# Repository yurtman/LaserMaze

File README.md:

LaserMaze is an exciting game that imitates the comically bad kind of laser security system found in heist movies. Using Arduino, augmented laser pointers, and a smoke machine, LaserMaze can transform any shipping container or hallway into a practice course for aspiring special agents.

It is currently still very much a prototype and the documentation of the project reflects this. For the most up to date documentation please see the [wiki](https://github.com/yurtman/LaserMaze/wiki).

##Features
- Made with easy to source components (laserpointers, basic electronics)
- Entrance/exit portal to start and stop the timer
- Auto calibration
- Steal detection (item to be stolen can be easily customised)
- Alarm sequence
- Open source

###Not yet implemented but being worked on:
- GUI to display high scores and alignment status (done in the processing language)
- scaling to the arduino Mega to include more lasers
- LED alarm lights integrated with the hardware and code
- sound effects and speaker (Alarm, Maze Active, enter the maze)
- expanding the current positioning strategies
- wireless communication and battery modules

###Abandoned goals:
- videofeed so attendant doens't need to stand inside the smoke filled container the whole day (IR light is also blocked by smoke... duh!)
- moving lasers (nice in the movies, very hard to actually make)

##Examples of use
The LaserMaze started as a hobby project with humble beginnings- a rats nest of alligator clips. 

Since then development has not improved much but the experience resonates well with audiences of all ages and the prototype has already been used for quite a few events:
####Orbit Festival (21st Dec 2014)

####Open day De Jonge Onderzoekers (14th Feb 2015)

####Maak Festival Groningen (12th Apr 2015)

####Night of Art and Science (5th Jun 2015)

####Noorderzon Festival (26th-30th Aug 2015)

####Kinderboekenweek (10th Oct 2015)

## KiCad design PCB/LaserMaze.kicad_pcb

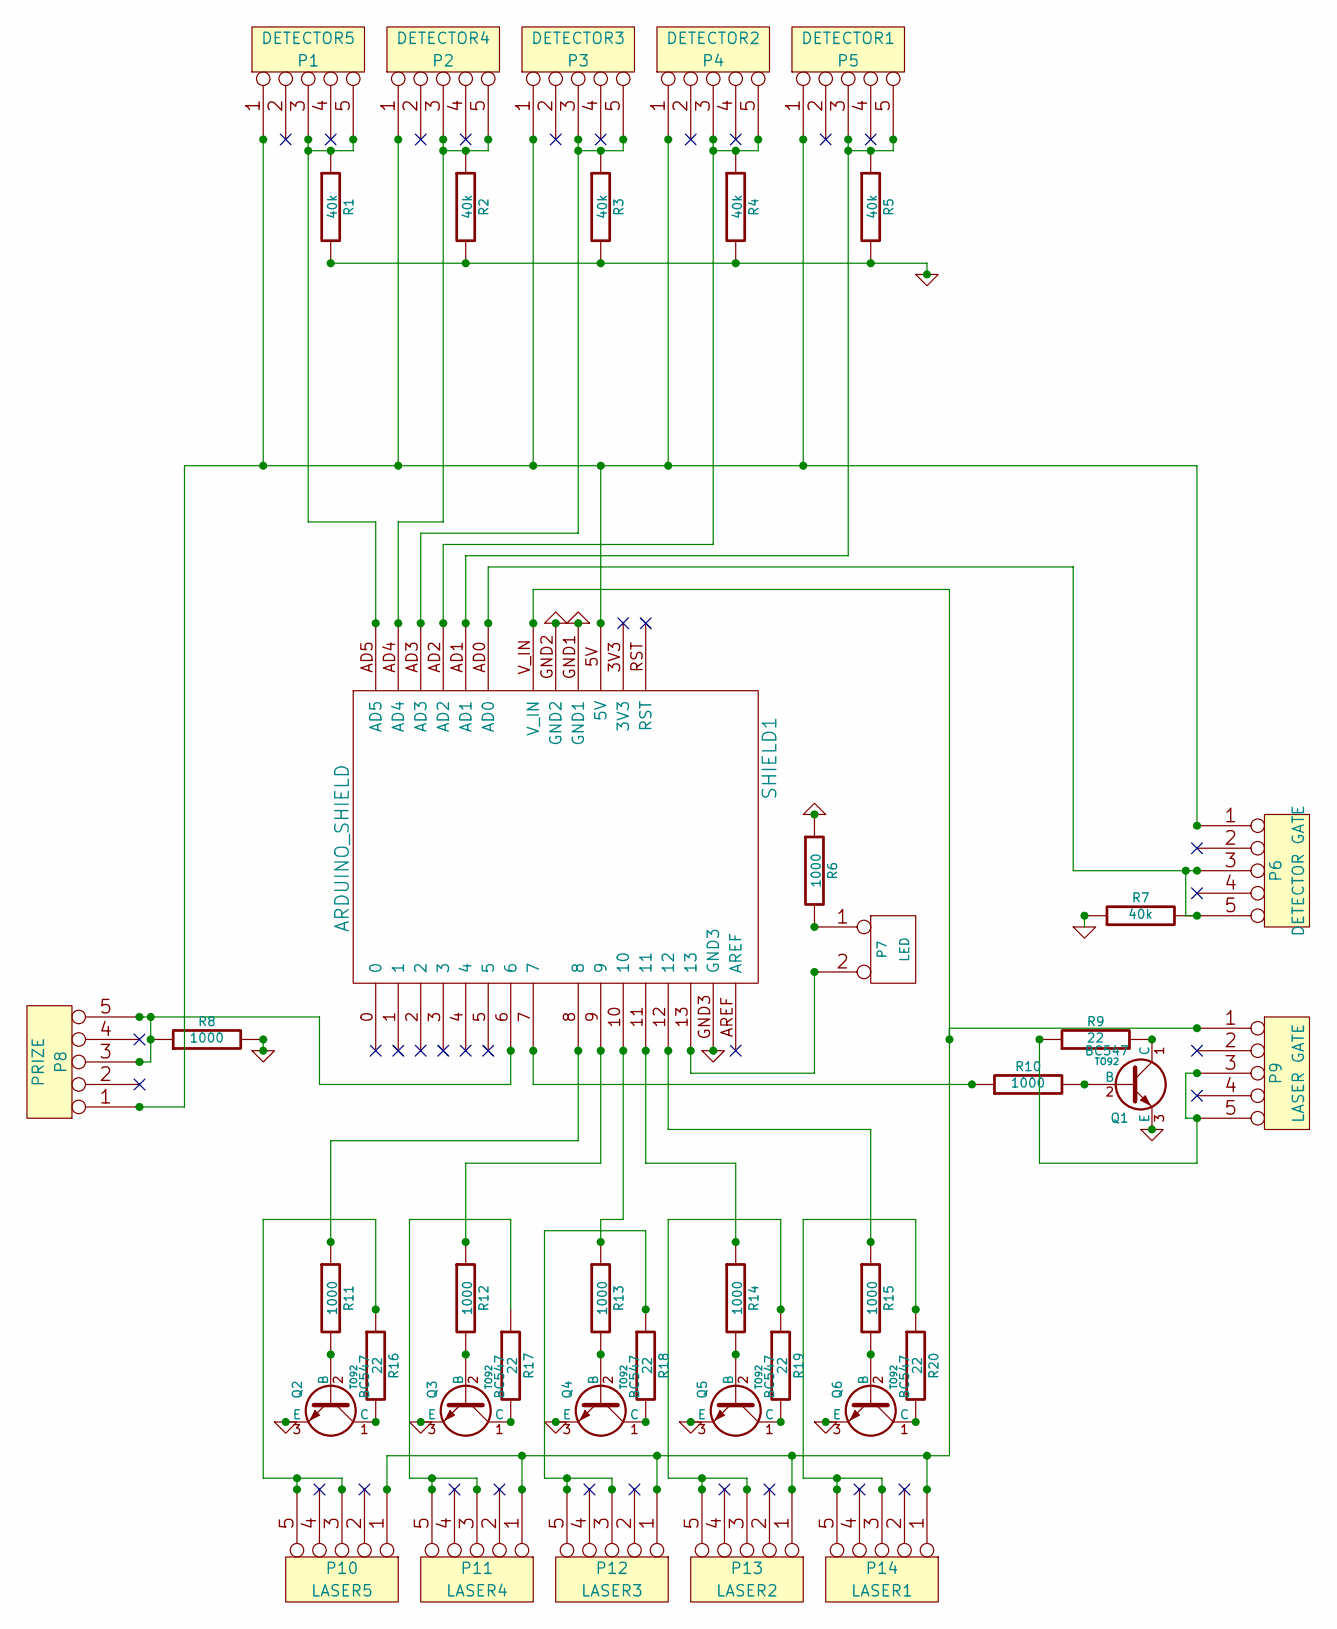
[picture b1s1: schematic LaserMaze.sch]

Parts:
P1: DETECTOR5
P2: DETECTOR4
P3: DETECTOR3
P4: DETECTOR2
P5: DETECTOR1
P6: DETECTOR GATE
P7: LED
P8: PRIZE
P9: LASER GATE
P10: LASER5
P11: LASER4
P12: LASER3
P13: LASER2
P14: LASER1
Q1, Q2, Q3, Q4, Q5, Q6: BC547; TO92
R1, R2, R3, R4, R5, R7: 40k
R6, R8, R10, R11, R12, R13, R14, R15: 1000
R9, R16, R17, R18, R19, R20: 22
SHIELD1: ARDUINO_SHIELD

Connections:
GND: Q1.3 (E), Q2.3 (E), Q3.3 (E), Q4.3 (E), Q5.3 (E), Q6.3 (E), R1.2, R2.2, R3.2, R4.2, R5.2, R6.1, R7.1, R8.2, SHIELD1.GND1, SHIELD1.GND2, SHIELD1.GND3
unnamed: P9.1, P10.1, P11.1, P12.1, P13.1, P14.1, SHIELD1.V_IN
unnamed: P7.2 (PM), SHIELD1.13
unnamed: R15.1, SHIELD1.12
unnamed: R14.1, SHIELD1.11
unnamed: P1.1, P2.1, P3.1, P4.1, P5.1, P6.1, P8.1, SHIELD1.5V
unnamed: P9.3, P9.5, R9.1
unnamed: R13.1, SHIELD1.10
unnamed: R12.1, SHIELD1.9
unnamed: R11.1, SHIELD1.8
unnamed: R10.1, SHIELD1.7
unnamed: P6.3, P6.5, R7.2, SHIELD1.AD0
unnamed: Q3.2 (B), R12.2
unnamed: Q1.2 (B), R10.2
unnamed: Q1.1 (C), R9.2
unnamed: Q6.2 (B), R15.2
unnamed: Q6.1 (C), R20.2
unnamed: Q5.2 (B), R14.2
unnamed: Q5.1 (C), R19.2
unnamed: Q4.2 (B), R13.2
unnamed: Q4.1 (C), R18.2
unnamed: Q3.1 (C), R17.2
unnamed: Q2.2 (B), R11.2
unnamed: Q2.1 (C), R16.2
unnamed: P1.3, P1.5, R1.1, SHIELD1.AD5
unnamed: P2.3, P2.5, R2.1, SHIELD1.AD4
unnamed: P8.3, P8.5, R8.1, SHIELD1.6
unnamed: P13.3, P13.5, R19.1
unnamed: P12.3, P12.5, R18.1
unnamed: P11.3, P11.5, R17.1
unnamed: P14.3, P14.5, R20.1
unnamed: P10.3, P10.5, R16.1
unnamed: P3.3, P3.5, R3.1, SHIELD1.AD3
unnamed: P4.3, P4.5, R4.1, SHIELD1.AD2
unnamed: P5.3, P5.5, R5.1, SHIELD1.AD1
unnamed: P7.1, R6.2

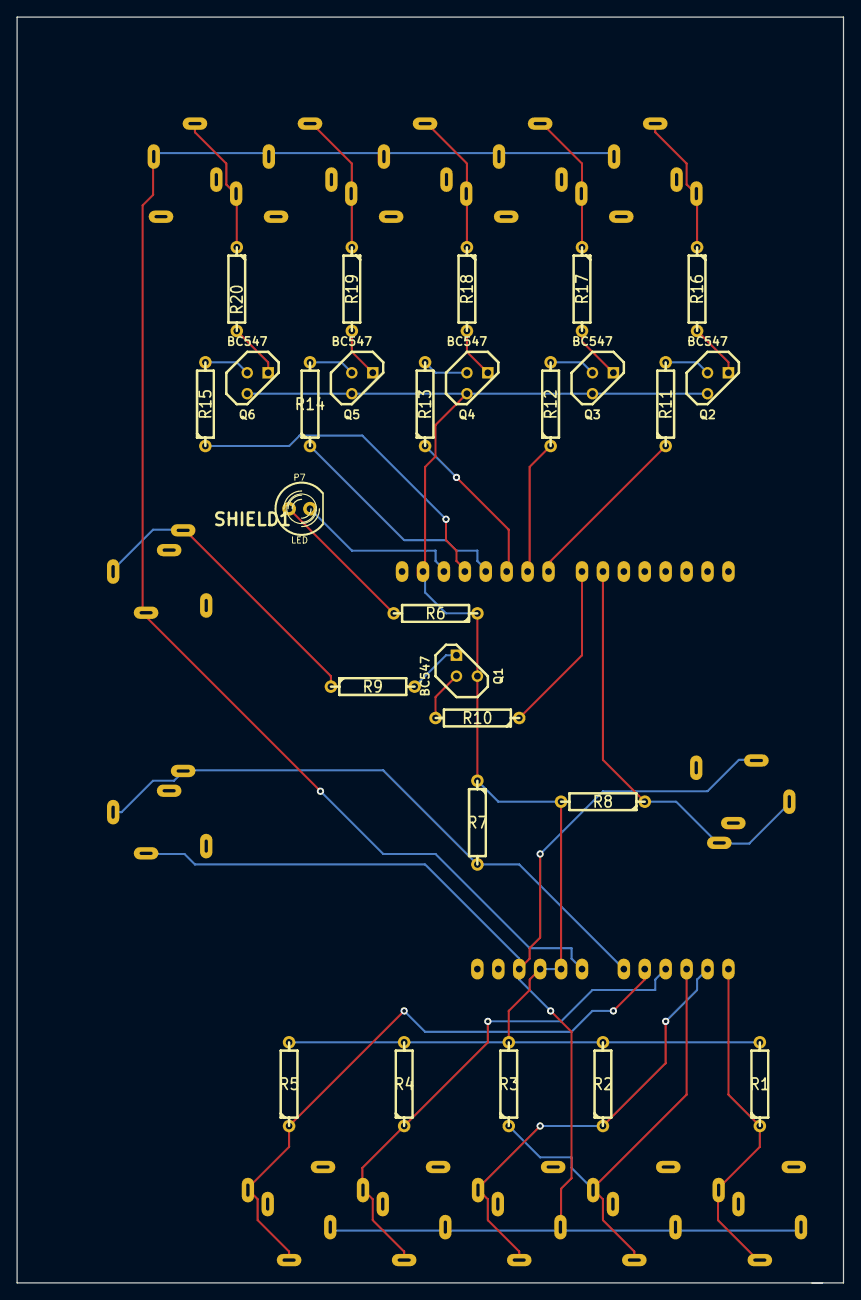
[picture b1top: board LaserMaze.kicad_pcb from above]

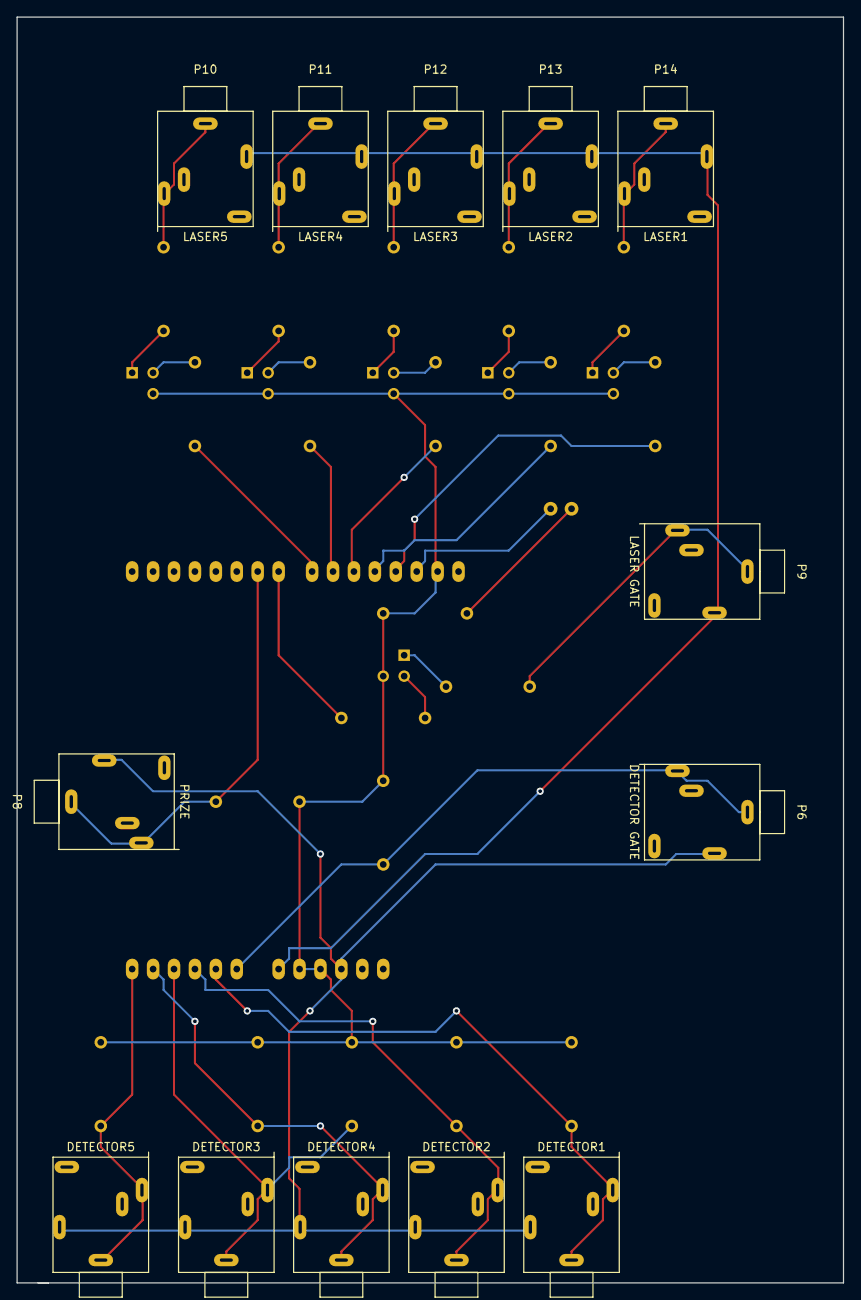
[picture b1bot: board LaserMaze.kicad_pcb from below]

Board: 2 copper layers, 100.3 x 153.7 mm, 41 parts (13 on the bottom side), 36 nets.

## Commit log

2015-01-08 First commit, arduino code, processing GUI barebones.
2015-02-20 added working alarm sketch RA2
2015-02-28 added some test sketches to the arduino forder, KiCAD design files for the PCB and some images
2015-02-28 changed the wiki to include images (test)
2015-02-28 changed the wiki to include images (test2)
2015-02-28 changed the wiki to include images (test3)
2015-03-02 Update README.md
    added dates to examples of use
2015-09-02 Update README.md
    minor update on the current situation
2015-11-25 updated images folder
2015-11-25 more pics
2015-11-25 new images
2015-11-28 image
2015-11-28 added kinderboekenweek foto
